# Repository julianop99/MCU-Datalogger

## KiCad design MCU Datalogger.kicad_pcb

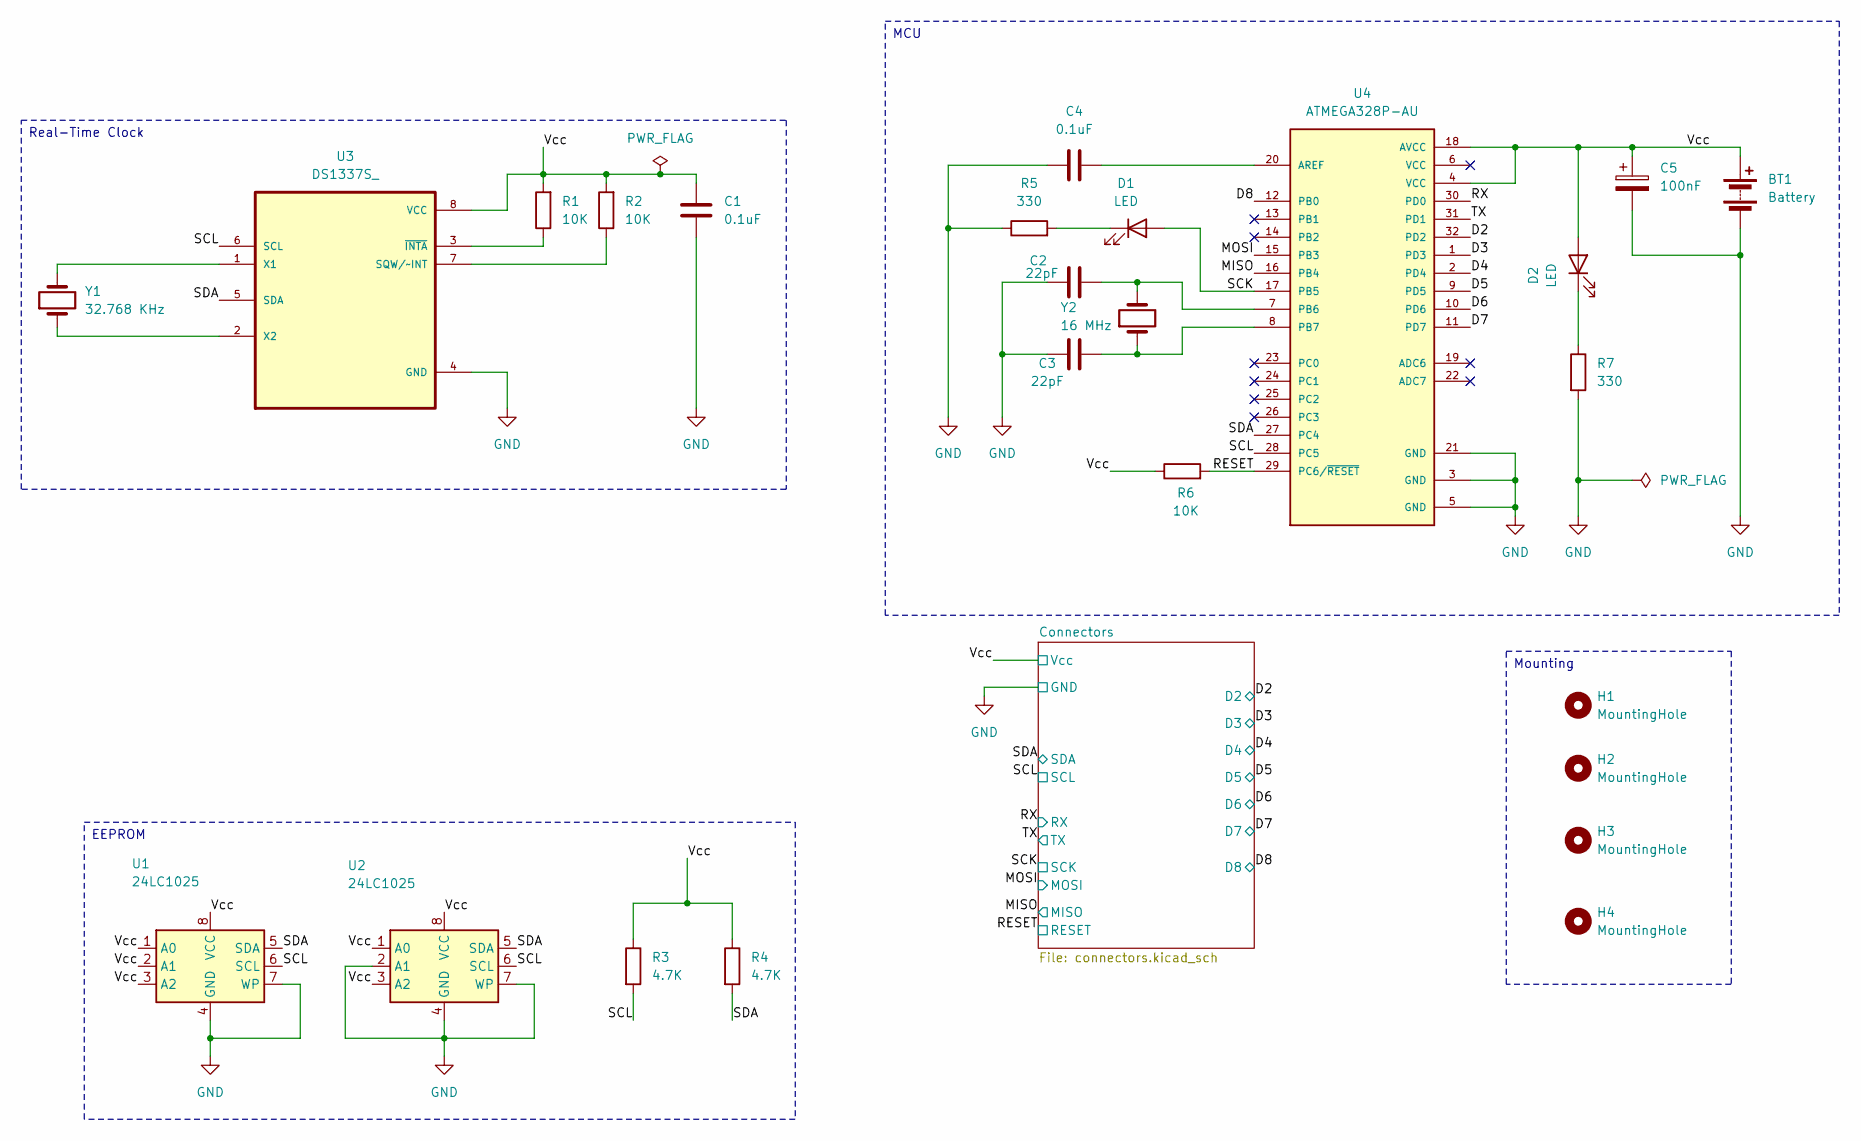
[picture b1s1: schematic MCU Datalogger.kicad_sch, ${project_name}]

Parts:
BT1: Battery; PinHeader_1x02_P2.54mm_Vertical
C1, C4: 0.1uF; C_0805_2012Metric
C2, C3: 22pF; C_0805_2012Metric
C5: 100nF; C_0805_2012Metric
D1, D2: LED; LED_0805_2012Metric
H1, H2, H3, H4: MountingHole; MountingHole_2.1mm
R1, R2, R6: 10K; R_0805_2012Metric
R3, R4: 4.7K; R_0805_2012Metric
R5, R7: 330; R_0805_2012Metric
U1, U2: 24LC1025; SOIC-8_5.3x5.3mm_P1.27mm
U3: DS1337S_; SOIC127P600X175-8N
U4: ATMEGA328P-AU; QFP80P900X900X120-32N; PARTREV 8271A; DigiKey_Part_Number ATMEGA328P-AU-ND
Y1: 32.768 KHz; Crystal_SMD_3215-2Pin_3.2x1.5mm
Y2: 16 MHz; Crystal_SMD_5032-2Pin_5.0x3.2mm_HandSoldering

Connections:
/D2: U4.32 (PD2); also elsewhere on the board
/D3: U4.1 (PD3); also elsewhere on the board
/D4: U4.2 (PD4); also elsewhere on the board
/D5: U4.9 (PD5); also elsewhere on the board
/D6: U4.10 (PD6); also elsewhere on the board
/D7: U4.11 (PD7); also elsewhere on the board
/D8: U4.12 (PB0); also elsewhere on the board
/MISO: U4.16 (PB4); also elsewhere on the board
/MOSI: U4.15 (PB3); also elsewhere on the board
/RESET: R6.2, U4.29 (PC6/~RESET); also elsewhere on the board
/RX: U4.30 (PD0); also elsewhere on the board
/SCK: D1.2 (A), U4.17 (PB5); also elsewhere on the board
/SCL: R3.2, U1.6 (SCL), U2.6 (SCL), U3.6 (SCL), U4.28 (PC5); also elsewhere on the board
/SDA: R4.2, U1.5 (SDA), U2.5 (SDA), U3.5 (SDA), U4.27 (PC4); also elsewhere on the board
/TX: U4.31 (PD1); also elsewhere on the board
/Vcc: BT1.1 (+), C1.1, C5.1, D2.2 (A), R1.2, R2.2, R3.1, R4.1, R6.1, U1.1 (A0), U1.2 (A1), U1.3 (A2), U1.8 (VCC), U2.1 (A0), U2.3 (A2), U2.8 (VCC), U3.8 (VCC), U4.4 (VCC), U4.18 (AVCC); also elsewhere on the board
GND: BT1.2 (-), C1.2, C2.1, C3.1, C4.1, C5.2, R5.1, R7.2, U1.4 (GND), U1.7 (WP), U2.2 (A1), U2.4 (GND), U2.7 (WP), U3.4 (GND), U4.3 (GND), U4.5 (GND), U4.21 (GND); also elsewhere on the board
unnamed: D1.1 (K), R5.2
unnamed: D2.1 (K), R7.1
unnamed: R2.1, U3.7 (SQW/~INT)
unnamed 20: U3.1 (X1), Y1.2; also elsewhere on the board
unnamed 21: U3.2 (X2), Y1.1; also elsewhere on the board
unnamed: R1.1, U3.3 (~INTA)
unnamed: C4.2, U4.20 (AREF)
unnamed: C2.2, U4.7 (PB6), Y2.2
unnamed: C3.2, U4.8 (PB7), Y2.1

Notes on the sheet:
Mounting
Real-Time Clock
MCU
EEPROM

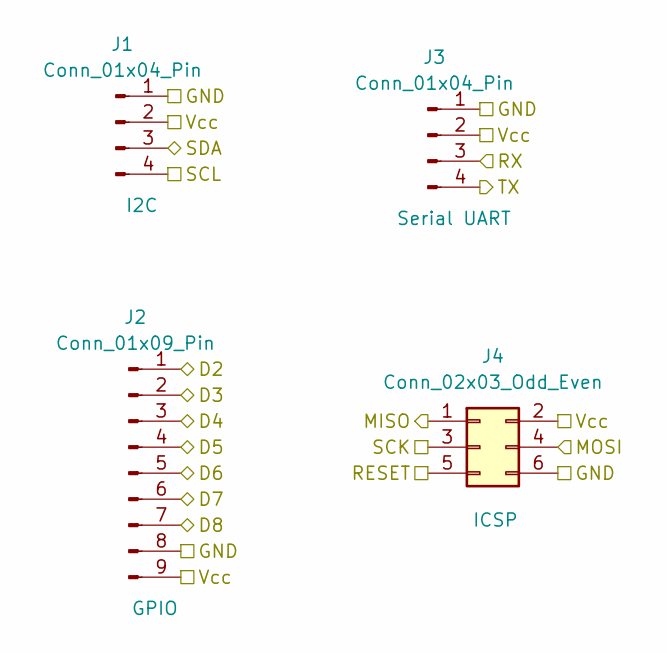
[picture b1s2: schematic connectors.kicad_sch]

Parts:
J1, J3: Conn_01x04_Pin; PinHeader_1x04_P2.54mm_Vertical
J2: Conn_01x09_Pin; PinHeader_1x09_P2.54mm_Vertical
J4: Conn_02x03_Odd_Even; PinHeader_2x03_P2.54mm_Vertical

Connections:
/D2: J2.1; also elsewhere on the board
/D3: J2.2; also elsewhere on the board
/D4: J2.3; also elsewhere on the board
/D5: J2.4; also elsewhere on the board
/D6: J2.5; also elsewhere on the board
/D7: J2.6; also elsewhere on the board
/D8: J2.7; also elsewhere on the board
/MISO: J4.1; also elsewhere on the board
/MOSI: J4.4; also elsewhere on the board
/RESET: J4.5; also elsewhere on the board
/RX: J3.3; also elsewhere on the board
/SCK: J4.3; also elsewhere on the board
/SCL: J1.4; also elsewhere on the board
/SDA: J1.3; also elsewhere on the board
/TX: J3.4; also elsewhere on the board
/Vcc: J1.2, J2.9, J3.2, J4.2; also elsewhere on the board
GND: J1.1, J2.8, J3.1, J4.6; also elsewhere on the board

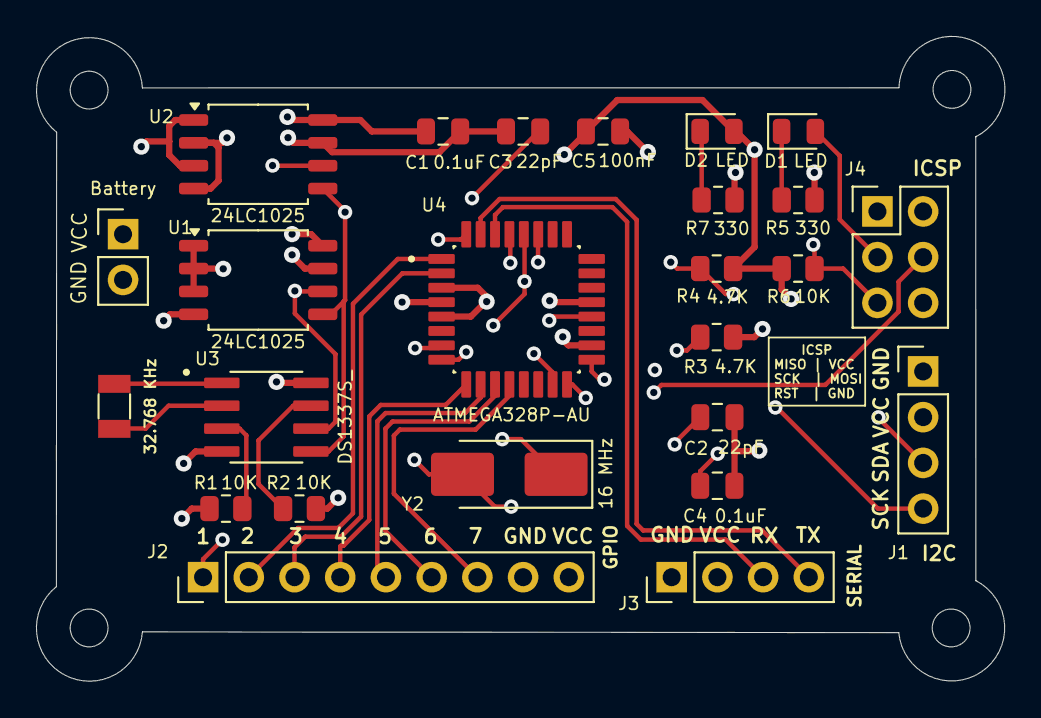
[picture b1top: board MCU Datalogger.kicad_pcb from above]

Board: 4 copper layers, 53.8 x 35.8 mm, 29 parts (0 on the bottom side), 26 nets.

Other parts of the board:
32.768 KHz: 32.768; Crystal_SMD_3215-2Pin_3.2x1.5mm

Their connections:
unnamed 20: 32.768 KHz.2; also elsewhere on the board
unnamed 21: 32.768 KHz.1; also elsewhere on the board

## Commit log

2025-10-13 first commit of new project.
2025-10-13 Setup of EESchema for new project
2025-10-14 Required Symbols Added
2025-10-14 Change location of symbols
2025-10-14 Added components values
2025-10-14 Footprints added
2025-10-14 Wiring Main Sheet Completed
2025-10-15 Wiring Second Sheet Completed
2025-10-15 Power Net Class Allocated
2025-10-15 Comments
2025-10-16 2-Layer Setup Pcbnew.
2025-10-16 Completed Placements of Footprints
2025-10-18 Routing sans GND Vcc complete
2025-10-26 Routing sans GND Vcc complete.
2025-10-26 Completed Routing.
2025-10-27 Refined Routing Completed
2025-10-27 Version for manufacturing
2025-10-28 Completed 2-layer PCB project
2025-10-29 Completed 2-layer PCB.
2025-10-29 Added gerber directories to .gitignore
2025-10-31 Initial routing 4 layers
2025-11-03 Completed routing 4 layers
2025-11-06 Added Board Characteristics at User 1 Layer
2025-11-06 Added Board Characteristics at User 1 Layer 2
2025-11-11 Fixed Bugs at 4layer
2025-11-12 Fixed Bugs in the 4layer PCB
2025-12-27 Sync 2layer variant
2025-12-27 Changed 32.768khz oscillator footprint from 5032 to 3215
2026-01-03 Updated 3215 32.768kHz Oscillator in the 4layer PCB
